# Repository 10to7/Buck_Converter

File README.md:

Buck Converter
==================

A couple of attempts at creating a buck converter.

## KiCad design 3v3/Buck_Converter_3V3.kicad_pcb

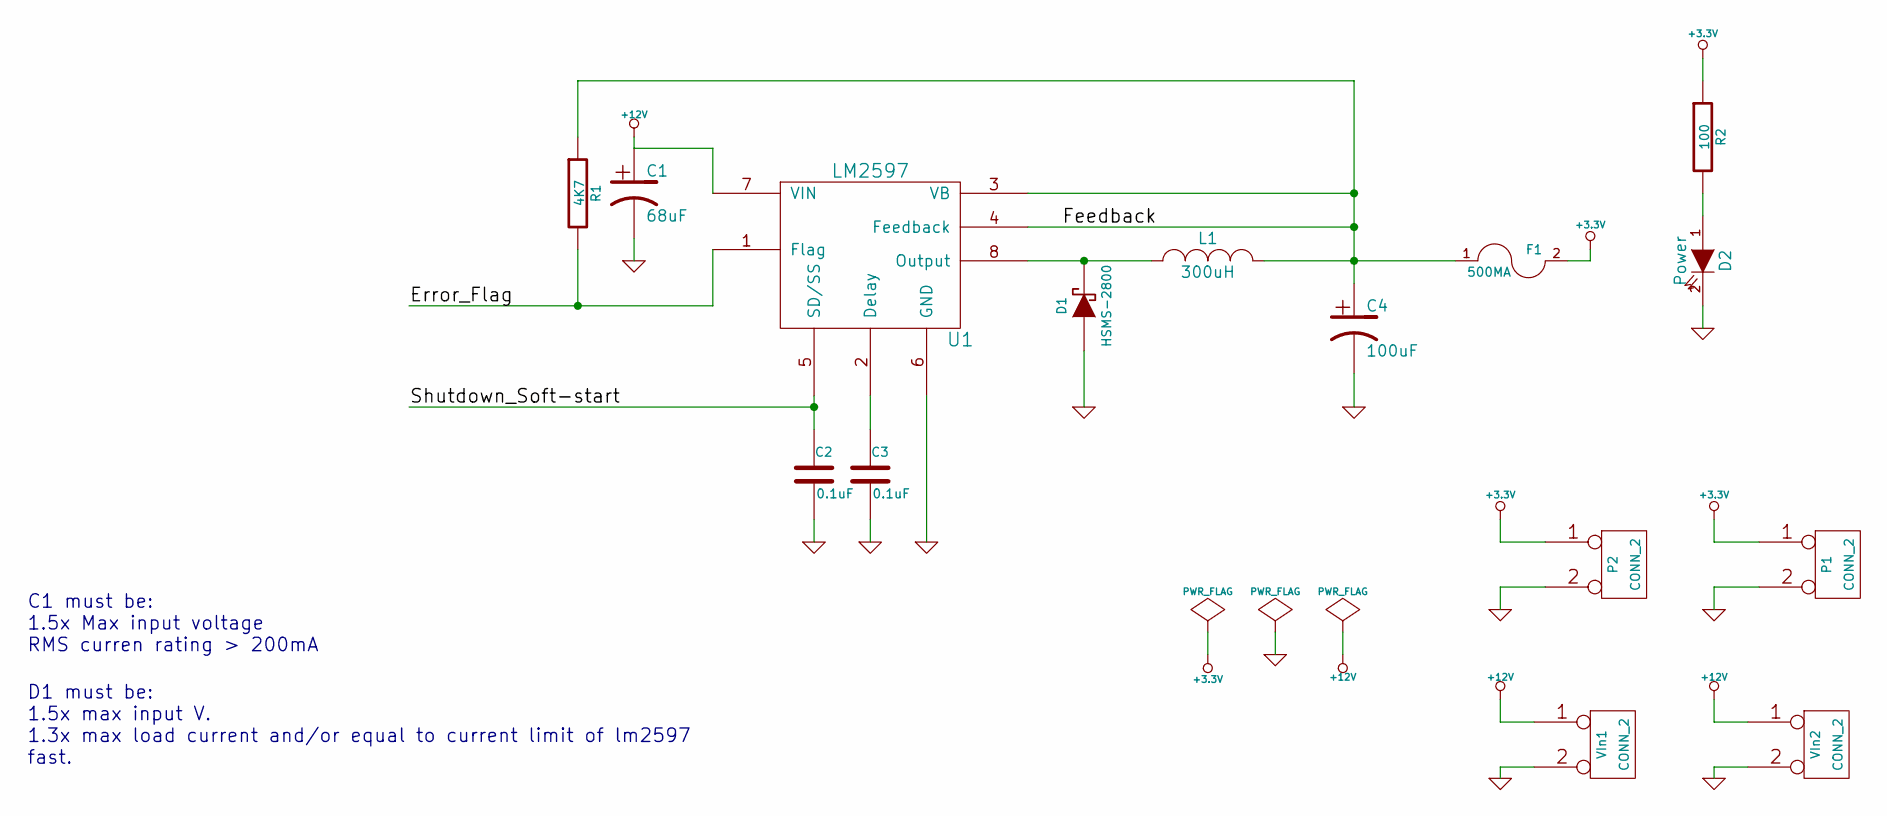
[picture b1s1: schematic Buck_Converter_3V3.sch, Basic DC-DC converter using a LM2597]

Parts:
C1: 68uF
C2, C3: 0.1uF
C4: 100uF
D1: HSMS-2800
D2: Power
F1: 500MA
L1: 300uH
P1, P2: CONN_2
R1: 4K7
R2: 100
U1: LM2597
VIn1, VIn2: CONN_2

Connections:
+3.3V: F1.2, P1.1, P2.1, R2.1
+12V: C1.1, U1.7 (VIN), VIn1.1, VIn2.1
/Error_Flag: R1.2, U1.1 (Flag)
/Feedback: C4.1, F1.1, L1.2, R1.1, U1.3 (VB), U1.4 (Feedback)
/Shutdown_Soft-start: C2.1, U1.5 (SD/SS)
GND: C1.2, C2.2, C3.2, C4.2, D1.1 (A), D2.2 (K), P1.2 (PM), P2.2 (PM), U1.6 (GND), VIn1.2 (PM), VIn2.2 (PM)
unnamed: C3.1, U1.2 (Delay)
unnamed: D1.2 (K), L1.1, U1.8 (Output)
unnamed: D2.1 (A), R2.2

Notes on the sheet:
D1 must be: 1.5x max input V. 1.3x max load current and/or equal to current limit of lm2597 fast.
C1 must be: 1.5x Max input voltage RMS curren rating > 200mA

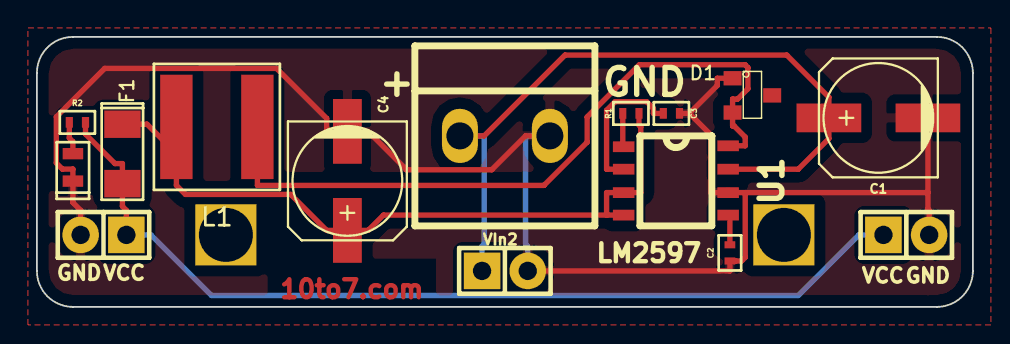
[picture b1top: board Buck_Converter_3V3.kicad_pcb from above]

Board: 2 copper layers, 52.0 x 15.0 mm, 17 parts (0 on the bottom side), 9 nets.

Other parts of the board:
3mmHole, 3mmHole_1: VAL**; 3mmHole

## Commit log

2014-06-02 Added new board
2014-06-20 updated to add a fuse and led
2014-07-15 Added additional pin input
2014-07-15 missed the final changes to the PCB from last commit.
2014-07-17 Added render of the buck converter
